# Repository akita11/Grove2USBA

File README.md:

# Grove2USBA

Grove端子から電源(+5V)をUSB-Aコネクタ（ソケット）への給電をGrove端子の信号線で制御することができます。

## 使い方

Grove端子をM5Stack等に接続し、給電したい機器をUSB-Aコネクタに接続します。Grove端子の信号線（初期状態では"A"(2番)）を"L"にすると給電され、"H"（または開放）にすると給電されません。

給電したい機器への電力はGrove端子から受けますので、供給側の電力供給が不足する場合は、[「M5Stack USB TypeC2Grove外部電源供給ユニット」](https://www.switch-science.com/products/8453)等をつかって電源を強化してください。

## 設定の変更

コネクタへの給電制御をGrove端子の2本の信号線のどちらで行うかを切り替えることができます。

- A(2番): JP2を中央-△マークのある側をショート（初期状態）
- B(1番): JP2を中央-△マークのない側をショート（※中央-△マークのある側のパターンをカットしてください）

## 使い方（オプション）

給電のためのUSB-Aプラグ、またはUSB-Cコネクタを追加でとりつけ、そちらから給電することができます。
これらを使う場合は、JP1をカット（初期状態はショート）することで、Grove端子からの+5V給電を切ることができます。

- USB-Aプラグ: [秋月電子・USB-4AM103AS](https://akizukidenshi.com/catalog/g/g102236/)等
- USB-Cコネクタ: [秋月電子・UJC-HP-3-SMT-TR](https://akizukidenshi.com/catalog/g/g116438/)等＋5.1kΩチップ抵抗(0603/1608)x2個

## Author

Junichi Akita (akita@ifdl.jp, @akita11)

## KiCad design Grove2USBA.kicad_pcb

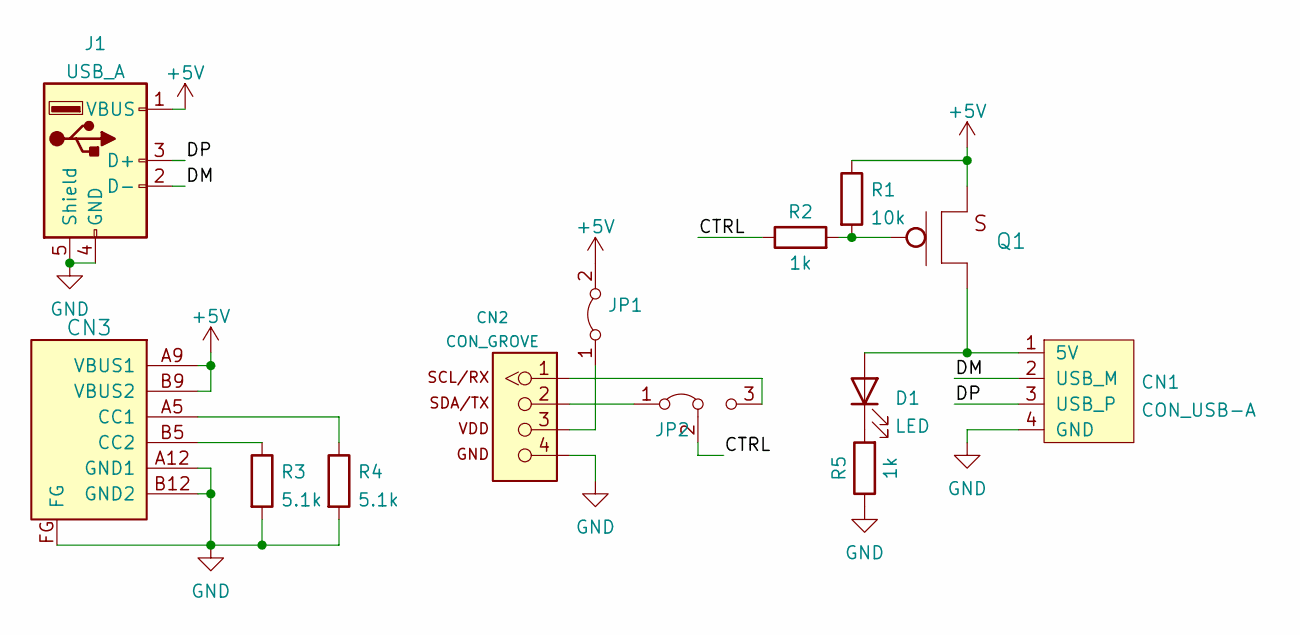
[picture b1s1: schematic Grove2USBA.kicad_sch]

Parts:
CN1: CON_USB-A; USB_A_Molex_67643_Horizontal
CN2: CON_GROVE; CON_GROVE_V
CN3: CON_USB-C-6; USB-C_6P
D1: LED; LED_0603_1608Metric
J1: USB_A; USB-A_plug
JP1: Jumper_2_Bridged; SolderJumper-2_P1.3mm_Bridged_Pad1.0x1.5mm
JP2: Jumper_3_Bridged12; SolderJumper-3_P1.3mm_Bridged12_Pad1.0x1.5mm
Q1: TR_PMOS_IRLML6402; SOT-23
R1: 10k; R_0603_1608Metric
R2, R5: 1k; R_0603_1608Metric
R3, R4: 5.1k; R_0603_1608Metric

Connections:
+5V: CN3.A9 (VBUS1), CN3.B9 (VBUS2), J1.1 (VBUS), JP1.2 (B), Q1.2 (S), R1.1
/CTRL: JP2.2 (C), R2.1
/DM: CN1.2 (USB_M), J1.2 (D-)
/DP: CN1.3 (USB_P), J1.3 (D+)
GND: CN1.4 (GND), CN2.4, CN3.A12 (GND1), CN3.B12 (GND2), CN3.FG, J1.4 (GND), J1.5 (Shield), R3.2, R4.2, R5.1
unnamed: CN1.1 (5V), D1.2 (A), Q1.3 (D)
unnamed: CN2.1, JP2.3 (B)
unnamed: CN2.2, JP2.1 (A)
unnamed: CN2.3, JP1.1 (A)
unnamed: CN3.A5 (CC1), R4.1
unnamed: CN3.B5 (CC2), R3.1
unnamed: D1.1 (K), R5.2
unnamed: Q1.1 (G), R1.2, R2.2

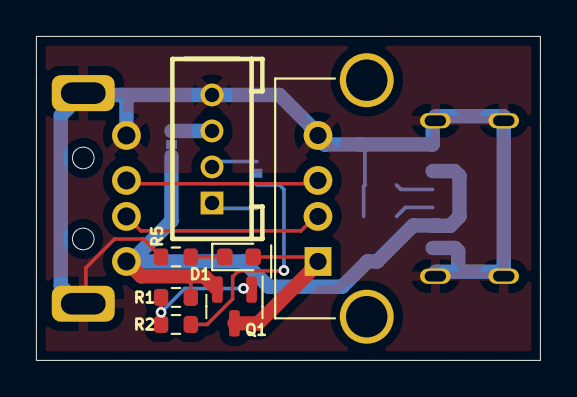
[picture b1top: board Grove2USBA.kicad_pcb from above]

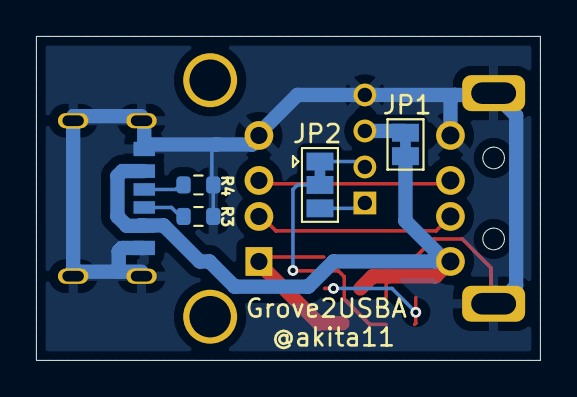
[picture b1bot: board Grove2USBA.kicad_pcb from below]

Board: 2 copper layers, 28.0 x 18.0 mm, 13 parts (5 on the bottom side), 13 nets.

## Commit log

2024-07-05 add photo
2024-07-05 typo fix
